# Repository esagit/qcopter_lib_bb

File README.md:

# Quadcopter - Breakout Board Adapter
Libelium SX1272 LoRa module Breakout Board Adapter for Arduino Mega
* [Libelium SX1272 LoRa module](https://www.cooking-hacks.com/sx1272-lora-module-for-arduino-raspberry-pi-intel-galileo-868-mhz)

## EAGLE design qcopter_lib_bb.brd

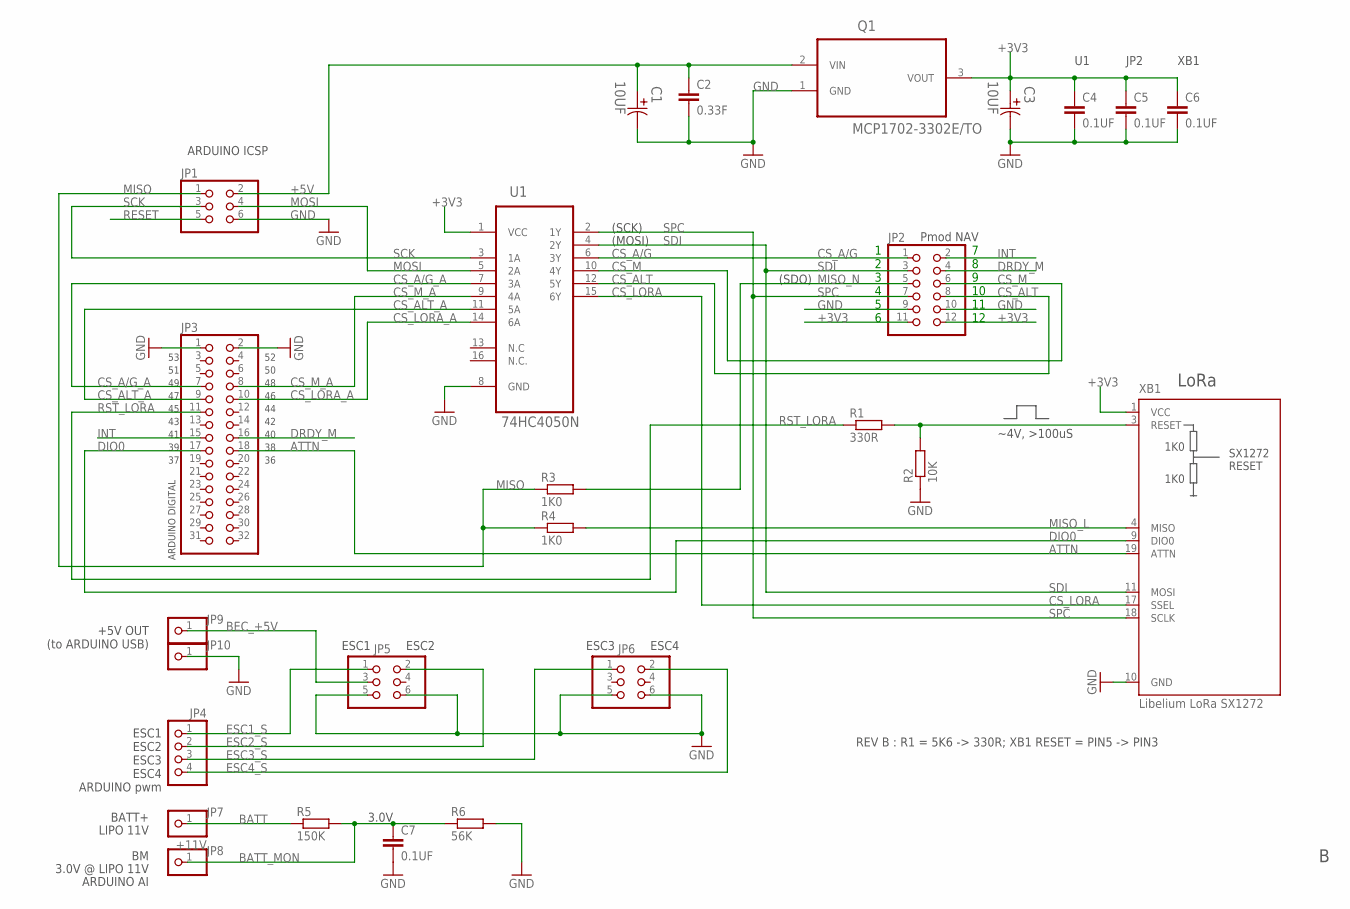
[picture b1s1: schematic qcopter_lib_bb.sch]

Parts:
C1, C3: 10UF; CAPPR200-500X1100
C2: 0.33F; C5B2.5
C4, C5, C6, C7: 0.1UF; C5B2.5
JP1, JP5, JP6: PINHD-2X3; 2X03
JP2: PINHD-2X6/90; 2X06/90
JP3: PINHD-2X16; 2X16
JP4: PINHD-1X4; 1X04
JP7: +11V; 1X01
JP8, JP9, JP10: PINHD-1X1; 1X01
Q1: MCP1702-3302E/TO; TO127P254X533-3
R1: 330R; 0207/10
R2: 10K; 0207/10
R3, R4: 1K0; 0207/10
R5: 150K; 0207/10
R6: 56K; 0207/10
U1: 74HC4050N; DIP254P762X420-16
XB1: Libelium LoRa SX1272; XBEE

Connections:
+3V3: C3.1, C4.1, C5.1, C6.1, JP2.11, JP2.12, Q1.3 (VOUT), U1.1 (VCC), XB1.1 (VCC)
+5V: C1.1, C2.1, JP1.2, Q1.2 (VIN)
ATTN: JP3.18, XB1.19 (ATTN)
BATT: JP7.1, R5.1
BATT_MON: C7.1, JP8.1, R5.2, R6.1
BEC_+5V: JP5.3, JP9.1
CS_A/G: JP2.1, U1.6 (3Y)
CS_A/G_A: JP3.7, U1.7 (3A)
CS_ALT: JP2.8, U1.12 (5Y)
CS_ALT_A: JP3.9, U1.11 (5A)
CS_LORA: U1.15 (6Y), XB1.17 (SSEL)
CS_LORA_A: JP3.10, U1.14 (6A)
CS_M: JP2.6, U1.10 (4Y)
CS_M_A: JP3.8, U1.9 (4A)
DIO0: JP3.17, XB1.9 (DIO0)
DRDY_M: JP2.4, JP3.16
ESC1_S: JP4.1, JP5.1
ESC2_S: JP4.2, JP5.2
ESC3_S: JP4.3, JP6.1
ESC4_S: JP4.4, JP6.2
GND: C1.2, C2.2, C3.2, C4.2, C5.2, C6.2, C7.2, JP1.6, JP2.9, JP2.10, JP3.1, JP3.2, JP5.5, JP5.6, JP6.5, JP6.6, JP10.1, Q1.1 (GND), R2.1, R6.2, U1.8 (GND), XB1.10 (GND)
INT: JP2.2, JP3.15
MISO: JP1.1, R3.1, R4.1
MISO_L: R4.2, XB1.4 (MISO)
MISO_N: JP2.5, R3.2
MOSI: JP1.4, U1.5 (2A)
unnamed: R1.2, R2.2, XB1.3 (RESET)
RESET: JP1.5
RST_LORA: JP3.11, R1.1
SCK: JP1.3, U1.3 (1A)
SDI: JP2.3, U1.4 (2Y), XB1.11 (MOSI)
SPC: JP2.7, U1.2 (1Y), XB1.18 (SCLK)

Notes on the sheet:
(SCK)
(MOSI)
(SDO)
JP2
XB1
ARDUINO ICSP
ARDUINO DIGITAL
Pmod NAV
LoRa
1 2 3 4 5 6
7 8 9 10 11 12
ESC1 ESC2 ESC3 ESC4 ARDUINO pwm
BATT+
3.0V @ LIPO 11V
3.0V
LIPO 11V
+5V OUT (to ARDUINO USB)
ESC2
ESC1
ESC3
ESC4
ARDUINO AI
~4V, >100uS
1K0
SX1272 RESET
REV B : R1 = 5K6 -> 330R; XB1 RESET = PIN5 -> PIN3

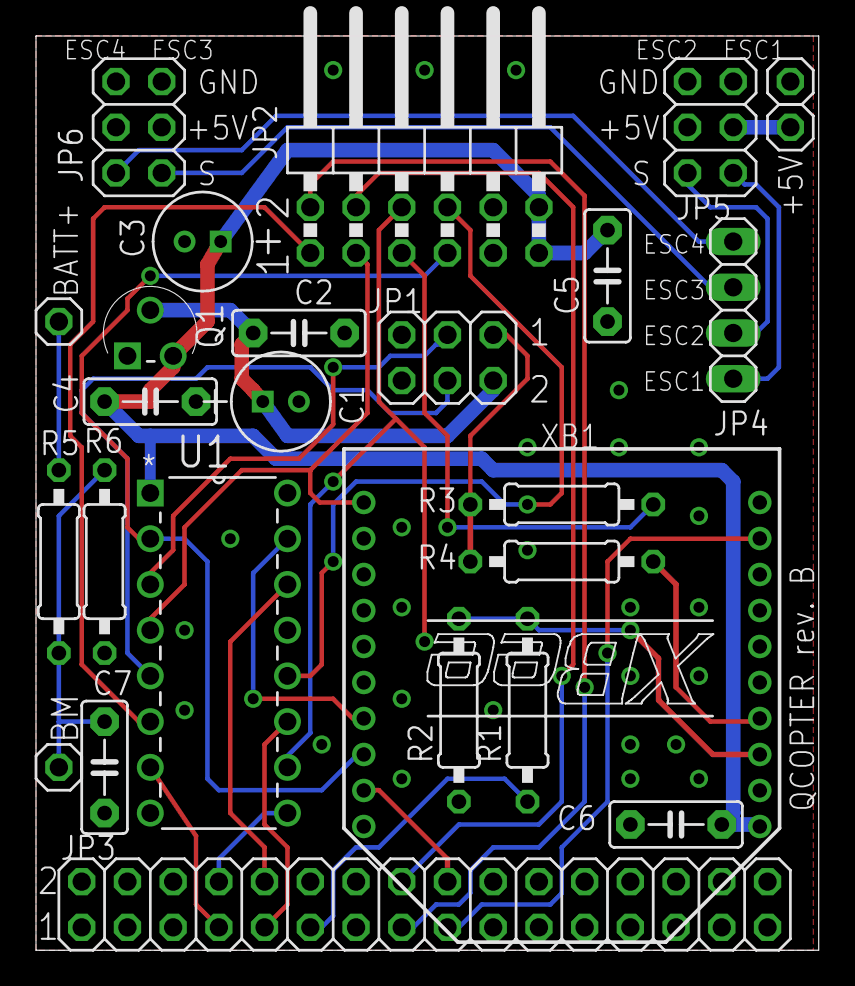
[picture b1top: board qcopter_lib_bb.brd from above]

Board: 2 copper layers, 43.5 x 50.8 mm, 26 parts (0 on the bottom side), 31 nets.

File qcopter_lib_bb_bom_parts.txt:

Partlist exported from C:/Users/Esa/Documents/eagle/qcopter_lib_bb/qcopter_lib_bb.sch at 24.8.2017 9.58

Part Value                Device           Package           Description                                       MPN              OC_FARNELL OC_NEWARK PACKAGE        SUPPLIER  TOLERANCE VALUE VOLTAGERATING
C1   10UF                 ECA1EHG470-D5XP2 CAPPR200-500X1100 Aluminum Electrolytic Capacitors/Radial Lead Type ECA1EHG470       1848541    17T5002   Radial Lead-TH PANASONIC ±20 %     47UF  25V          
C2   0.33F                C5/2.5           C5B2.5            CAPACITOR                                                                                                                                     
C3   10UF                 ECA1EHG470-D5XP2 CAPPR200-500X1100 Aluminum Electrolytic Capacitors/Radial Lead Type ECA1EHG470       1848541    17T5002   Radial Lead-TH PANASONIC ±20 %     47UF  25V          
C4   0.1UF                C5/2.5           C5B2.5            CAPACITOR                                                                                                                                     
C5   0.1UF                C5/2.5           C5B2.5            CAPACITOR                                                                                                                                     
C6   0.1UF                C5/2.5           C5B2.5            CAPACITOR                                                                                                                                     
C7   0.1UF                C5/2.5           C5B2.5            CAPACITOR                                                                                                                                     
JP1                       PINHD-2X3        2X03              PIN HEADER                                                                                                                                    
JP2                       PINHD-2X6/90     2X06/90           PIN HEADER                                                                                                                                    
JP3                       PINHD-2X16       2X16              PIN HEADER                                                                                                                                    
JP4                       PINHD-1X4        1X04              PIN HEADER                                                                                                                                    
JP5                       PINHD-2X3        2X03              PIN HEADER                                                                                                                                    
JP6                       PINHD-2X3        2X03              PIN HEADER                                                                                                                                    
JP7  +11V                 PINHD-1X1        1X01              PIN HEADER                                                                                                                                    
JP8                       PINHD-1X1        1X01              PIN HEADER                                                                                                                                    
JP9                       PINHD-1X1        1X01              PIN HEADER                                                                                                                                    
JP10                      PINHD-1X1        1X01              PIN HEADER                                                                                                                                    
Q1   MCP1702-3302E/TO     MCP1702-3302E/TO TO127P254X533-3   IC, V REG, LDO, 250MA                             MCP1702-3302E/TO 1331485    34M7419   TO-92          Microchip                              
R1   330R                 R-EU_0207/10     0207/10           RESISTOR, European symbol                                                                                                                     
R2   10K                  R-EU_0207/10     0207/10           RESISTOR, European symbol                                                                                                                     
R3   1K0                  R-EU_0207/10     0207/10           RESISTOR, European symbol                                                                                                                     
R4   1K0                  R-EU_0207/10     0207/10           RESISTOR, European symbol                                                                                                                     
R5   150K                 R-EU_0207/10     0207/10           RESISTOR, European symbol                                                                                                                     
R6   56K                  R-EU_0207/10     0207/10           RESISTOR, European symbol                                                                                                                     
U1   74HC4050N            74HC4050N        DIP254P762X420-16 Hex high-to-low level shifter,DIP-16              74HC4050N        380908     07WX3736  DIP-16         NXP                                    
XB1  Libelium LoRa SX1272 SX1272-LORA      XBEE

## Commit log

2017-08-24 :boom::camel: Added .gitattributes & .gitignore files
2017-08-24 Initial commit
    Initial commit
2017-08-24 Updated .cam files
    File: gerberfiles/%N.xxx
